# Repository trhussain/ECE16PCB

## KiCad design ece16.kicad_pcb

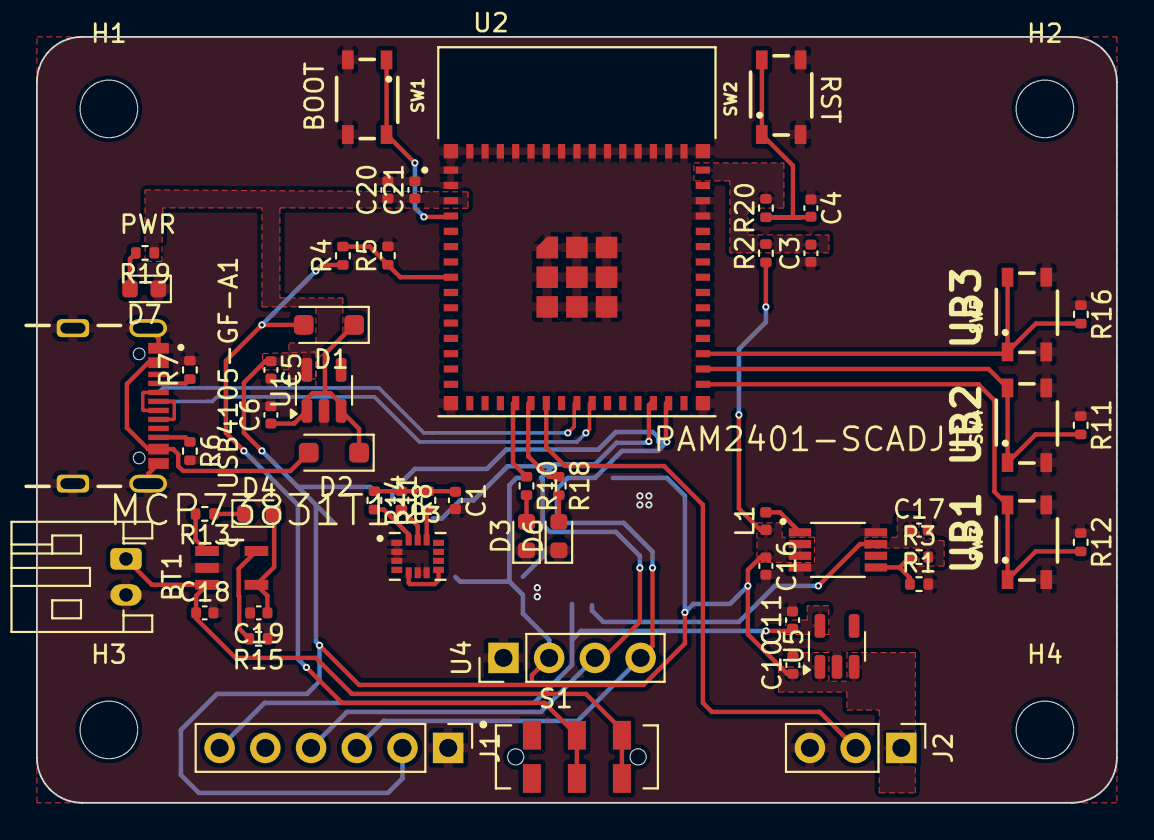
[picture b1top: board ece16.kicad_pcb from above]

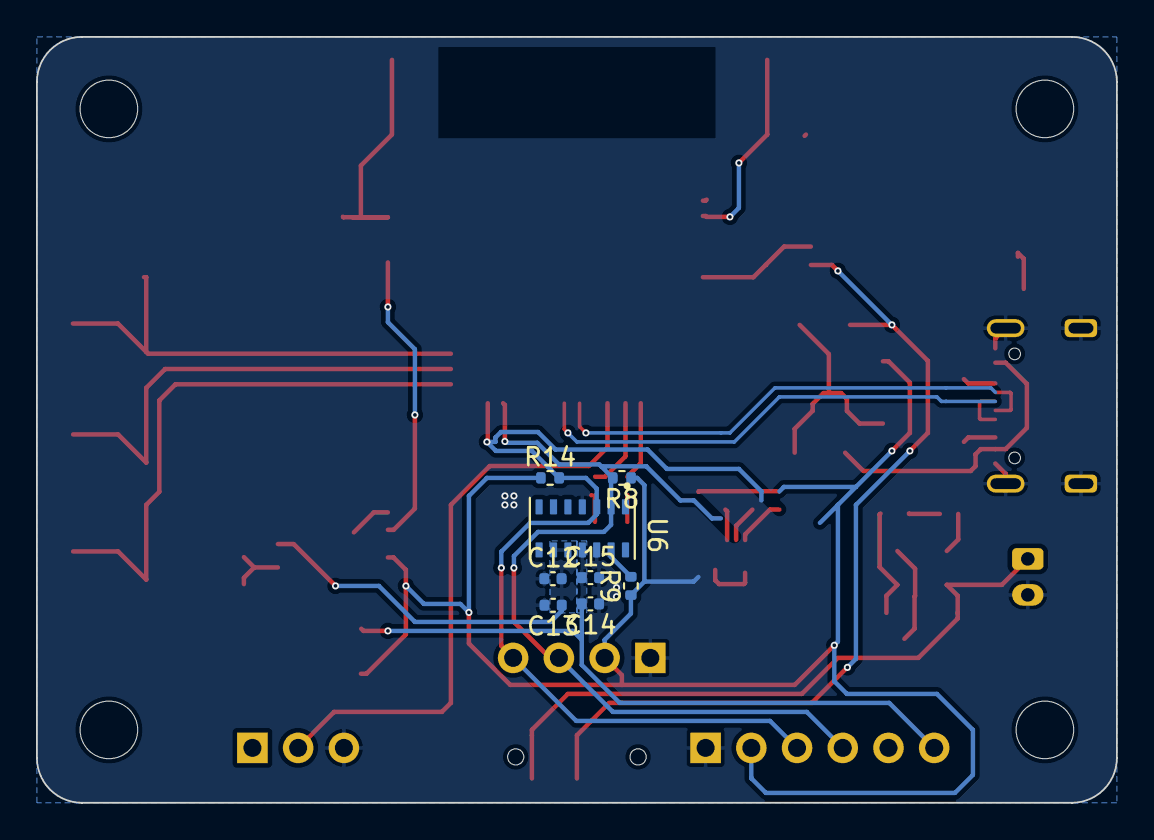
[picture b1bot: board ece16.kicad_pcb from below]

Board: 2 copper layers, 60.0 x 42.5 mm, 68 parts (8 on the bottom side), 34 nets.

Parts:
BT1: Battery_Cell; JST_PH_S2B-PH-K_1x02_P2.00mm_Horizontal
C1, C4, C13, C15, C21: 0.1uF; C_0402_1005Metric
C3, C5, C6, C10, C11: 1uF; C_0402_1005Metric
C12, C16: 10uF; C_0402_1005Metric
C14, C18, C19: 4.7uF; C_0402_1005Metric
C17, C20: 22uF; C_0402_1005Metric
D1, D2: D; D_SOD-123F
D3, D6, D7: LED; LED_0603_1608Metric
D4: LED CHRG; LED_0603_1608Metric
H1, H2, H3, H4: MountingHole; MountingHole_3.2mm_M3
J1: Conn_01x06_Socket; PinHeader_1x06_P2.54mm_Vertical
J2: Conn_01x03_Pin; PinHeader_1x03_P2.54mm_Vertical
L1: 2.2uH; L_0402_1005Metric
MCP73831T1: SOT95P270X145-5N
PAM2401-SCADJ1: SOP65P490X110-8N
R1: 100k; R_0402_1005Metric
R2, R20: 10k; R_0402_1005Metric
R3: 750k; R_0402_1005Metric
R4, R5, R6, R7: 5.1k; R_0402_1005Metric
R8, R8#2, R9, R11, R11#2, R12, R14, R14#2, R16: 1k; R_0402_1005Metric
R10, R18, R19: 510; R_0402_1005Metric
R13: 470; R_0402_1005Metric
R15: 2k; R_0402_1005Metric
S1: JS102011JAQN; SW_JS102011JAQN
SW1, SW2, SW3, SW4, SW5: rockerSwitch-434133025816
U1: LP5907MFX-3.3; SOT-23-5
U2: ESP32-S3-MINI-1-N8; XCVR_ESP32-S3-MINI-1-N8
U3: LSM6DSOXTR; PQFN50P250X300X86-14N
U4: DM-OLED096-636; PinHeader_1x04_P2.54mm_Vertical
U5: LP5907MFX-1.8; SOT-23-5
U6: MAX30101EFD_T; PSON80P560X330X165-14N
USB4105-GF-A1: GCT_USB4105-GF-A

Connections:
+1.8V: C11.1, C14.2, C15.1, J1.6, U5.5 (OUT), U6.11 (VDD)
+3V3: C1.1, C5.1, C10.1, C16.1, C20.1, C21.1, J1.2, J2.1, L1.1, PAM2401-SCADJ1.2 (EN), PAM2401-SCADJ1.3 (Vin), R2.1, R8.1, R8#2.1, R9.1, R11#2.2, R14.1, R14#2.1, R19.1, U1.5 (OUT), U2.3 (3V3), U3.5 (VDDIO), U3.8 (VDD), U4.2 (VCC_IN), U5.1 (IN), U5.3 (EN)
+5V: C19.1, D2.2 (A), D4.2 (A), MCP73831T1.4 (VDD), USB4105-GF-A1.A4_B9 (VBUS), USB4105-GF-A1.B4_A9 (VBUS)
+BATT: D1.2 (A), R4.1, S1.2, S1.2.1 (2)
/Boot: SW1.1, U2.4 (IO0)
/DN: U2.23 (IO19), USB4105-GF-A1.A7 (DN1), USB4105-GF-A1.B7 (DN1)
/DP: U2.24 (IO20), USB4105-GF-A1.A6 (DP1), USB4105-GF-A1.B6 (DP2)
/EN: C3.2, R2.2, R20.2, U2.45 (EN)
/SCL: J1.4, R8.2, R8#2.2, U2.28 (IO33), U3.13 (SCL), U4.3 (SCL), U6.2 (SCL)
/SDA: J1.3, R14.2, R14#2.2, U2.29 (IO34), U3.14 (SDA), U4.4 (SDA), U6.3 (SDA)
/T1: J2.2, U2.21 (IO17)
/U-LED1: R10.1, U2.19 (IO15)
/U-LED2: R18.1, U2.20 (IO16)
/UB1: R12.2, SW3.1, U2.31 (IO35)
/UB2: R11.2, SW4.1, U2.32 (IO36)
/UB3: R16.2, SW5.1, U2.33 (IO37)
/VLED: C12.2, C13.1, C17.1, PAM2401-SCADJ1.7 (OUT), R3.2, U6.9 (VLED+), U6.10 (VLED+)
GND: BT1.2 (-), C1.2, C3.1, C4.1, C5.2, C6.2, C10.2, C11.2, C12.1, C13.2, C14.1, C15.2, C16.2, C17.2, C18.2, C19.2, C20.2, C21.2, D3.1 (K), D6.1 (K), D7.1 (K), J1.1, J2.3, MCP73831T1.2 (VSS), PAM2401-SCADJ1.4 (AGND), PAM2401-SCADJ1.8 (PGND), R1.2, R5.2, R6.2, R7.2, R11.1, R12.1, R15.1, R16.1, SW1.2, SW2.2, SW3.2, SW4.2, SW5.2, U1.2 (GND), U2.1 (GND), U2.2 (GND), U2.42 (GND), U2.43 (GND), U2.46 (GND), U2.47 (GND), U2.48 (GND), U2.49 (GND), U2.50 (GND), U2.51 (GND), U2.52 (GND), U2.53 (GND), U2.54 (GND), U2.55 (GND), U2.56 (GND), U2.57 (GND), U2.58 (GND), U2.59 (GND), U2.60 (GND), U2.61 (GND), U2.61_1 (GND), U2.61_2 (GND), U2.61_3 (GND), U2.61_4 (GND), U2.61_5 (GND), U2.61_6 (GND), U2.61_7 (GND), U2.61_8 (GND), U2.62 (GND), U2.63 (GND), U2.64 (GND), U2.65 (GND), U3.1 (SDO/SA0), U3.2 (SDX), U3.3 (SCX), U3.6 (GND), U3.7 (GND), U4.1 (GND), U5.2 (GND), U6.4 (PGND), U6.12 (GND), USB4105-GF-A1.A1_B12 (GND), USB4105-GF-A1.B1_A12 (GND), USB4105-GF-A1.S1 (SHELL_GND), USB4105-GF-A1.S2 (SHELL_GND), USB4105-GF-A1.S3 (SHELL_GND), USB4105-GF-A1.S4 (SHELL_GND)
unnamed: BT1.1 (+), C18.1, MCP73831T1.3 (VBAT), S1.3, S1.3.1 (3)
unnamed: C4.2, R20.1, SW2.1
unnamed: C6.1, D1.1 (K), D2.1 (K), U1.1 (IN), U1.3 (EN)
unnamed: D3.2 (A), R10.2
unnamed: D4.1 (K), R13.1
unnamed: D6.2 (A), R18.2
unnamed: D7.2 (A), R19.2
unnamed: MCP73831T1.5 (PROG), R15.2
unnamed: MCP73831T1.1 (STAT), R13.2
unnamed: PAM2401-SCADJ1.5 (FB), R1.1, R3.1
unnamed: L1.2, PAM2401-SCADJ1.1 (LX)
unnamed: R4.2, R5.1, U2.8 (IO4)
unnamed: R11#2.1, U3.12 (CS)
unnamed: R9.2, U6.13 (~INT)
unnamed: R7.1, USB4105-GF-A1.A5 (CC1)
unnamed: R6.1, USB4105-GF-A1.B5 (CC2)

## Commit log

2024-06-22 Design of ordered board - Additional buttons for user config - Power indicator LEDs - Probe short issue between power rails and ground... Parallel diode config? Accomplished --------- N/A
    In Progress
    ---------
    N/A
    Errors
    ----------
    N/A
2024-06-24 Updated schematic Accomplished --------- N/A
    In Progress
    ---------
    N/A
    Errors
    ----------
    N/A
2024-09-27 Before you delete and reset everything
